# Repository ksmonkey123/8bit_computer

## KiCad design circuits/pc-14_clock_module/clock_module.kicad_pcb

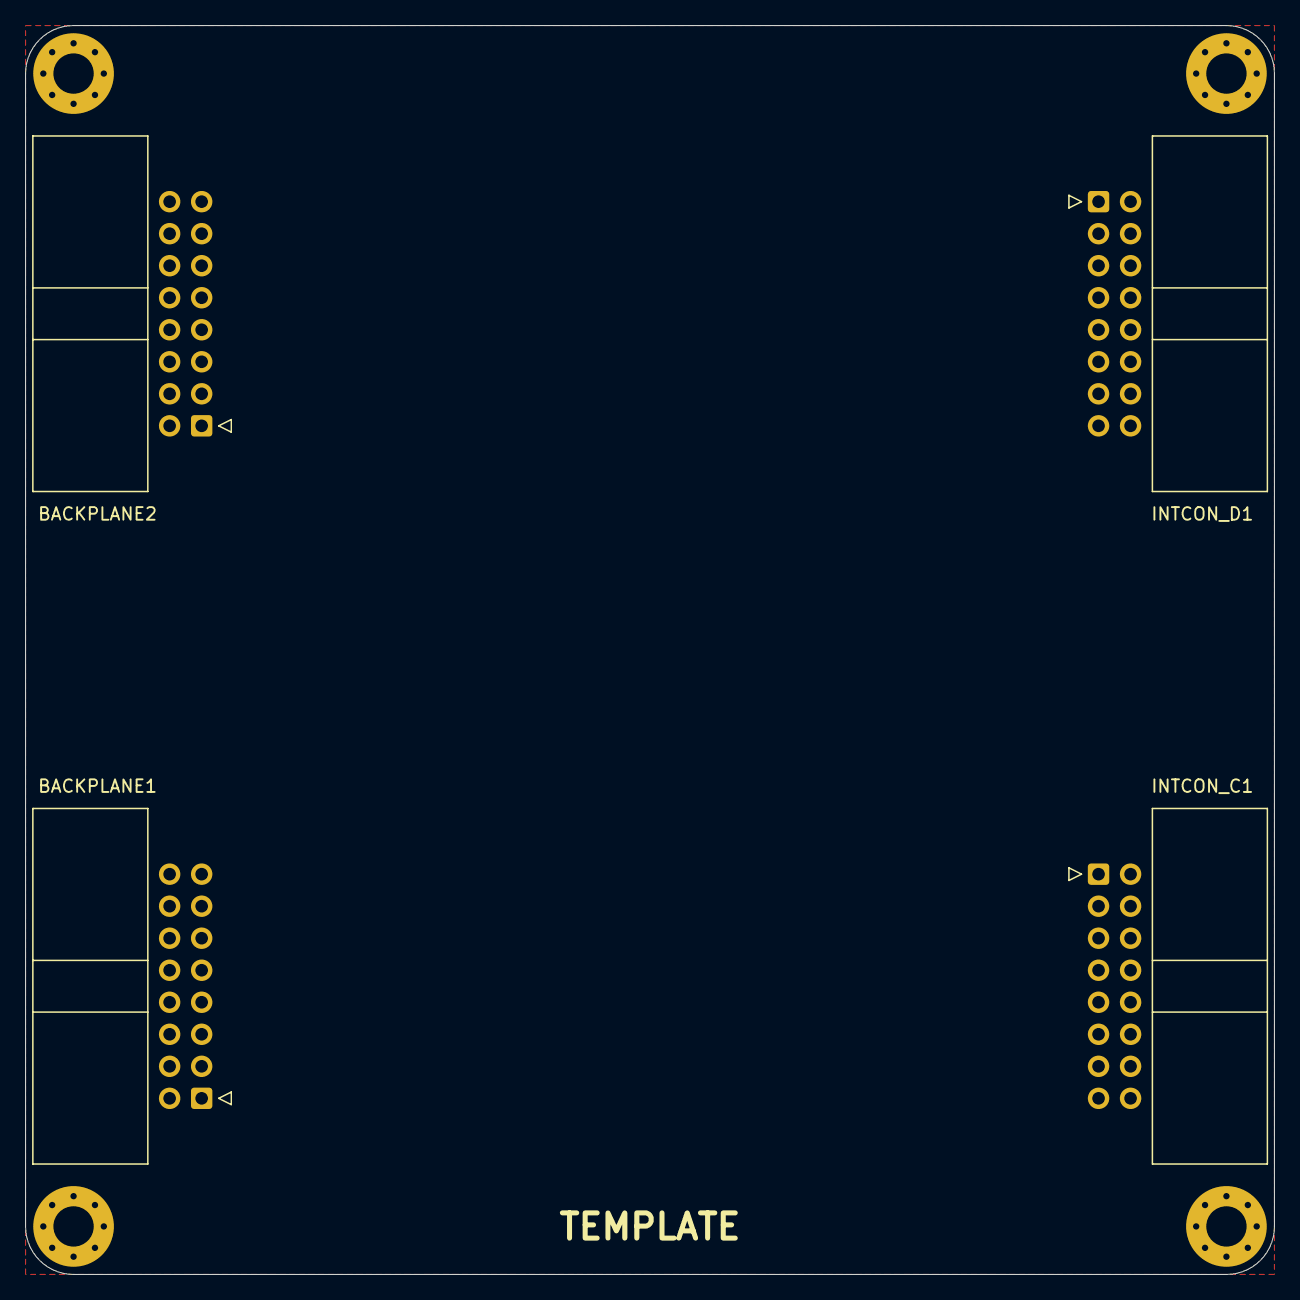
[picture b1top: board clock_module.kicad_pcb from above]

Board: 2 copper layers, 99.1 x 99.1 mm, 8 parts (0 on the bottom side), 4 nets, no tracks yet.

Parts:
BACKPLANE1, BACKPLANE2: Conn_01x16; IDC-Header_2x08_P2.54mm_Horizontal
H1, H2, H3, H4: MountingHole_Pad; MountingHole_3.2mm_M3_Pad_Via
INTCON_C1: Conn_01x16; IDC-Header_2x08_P2.54mm_Horizontal
INTCON_D1: Conn_01x16; IDC-Header_2x08_P2.54mm_Horizontal

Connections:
/clock: BACKPLANE1.1, INTCON_C1.8
/~reset: BACKPLANE1.3, INTCON_D1.12
GND: BACKPLANE1.13, BACKPLANE1.14, BACKPLANE1.15, BACKPLANE1.16, H1.1, H2.1, H3.1, H4.1, INTCON_D1.15, INTCON_D1.16
VCC: BACKPLANE1.9, BACKPLANE1.10, BACKPLANE1.11, BACKPLANE1.12, INTCON_D1.13, INTCON_D1.14

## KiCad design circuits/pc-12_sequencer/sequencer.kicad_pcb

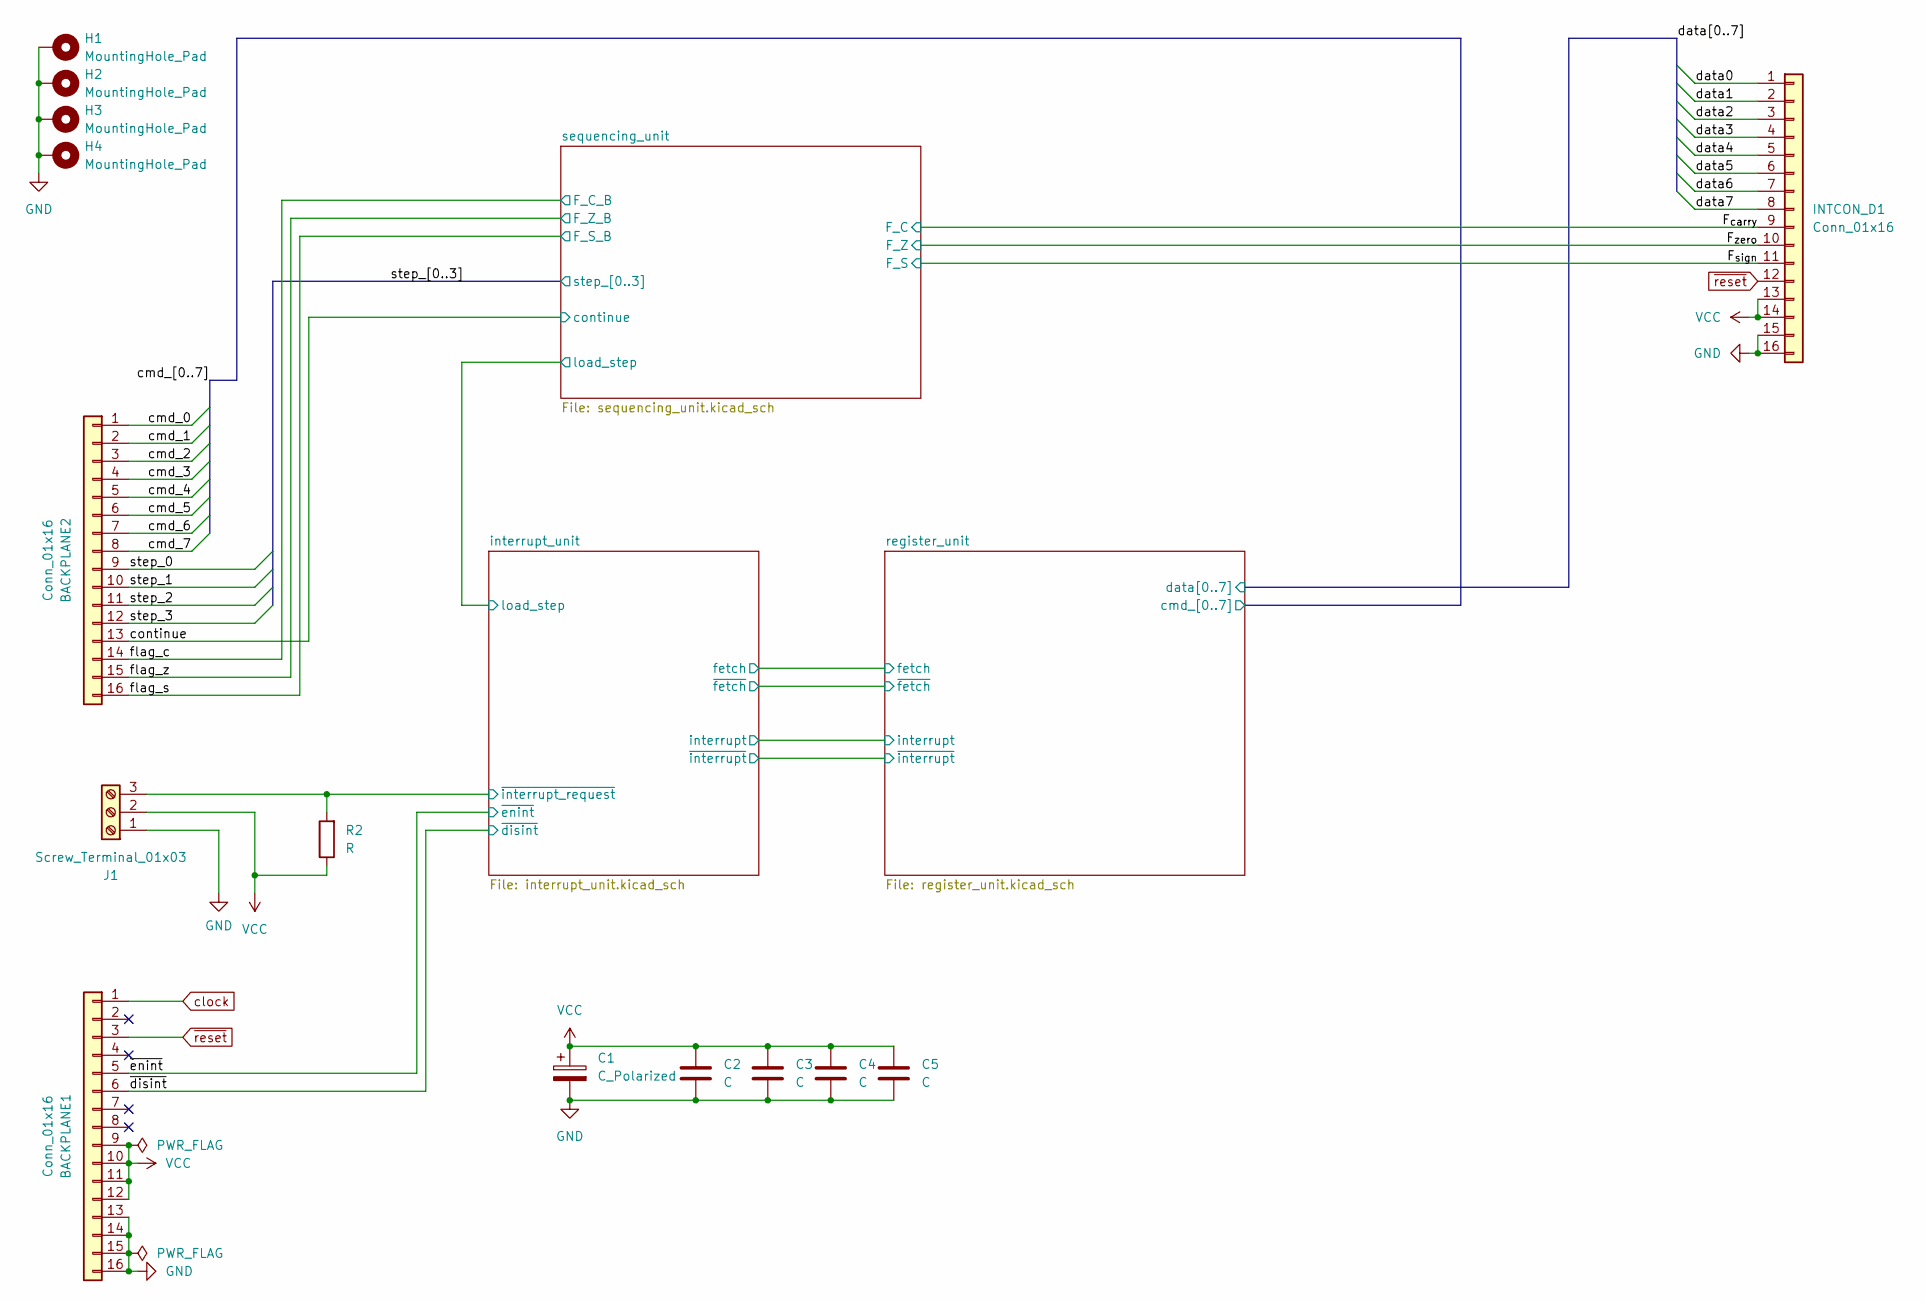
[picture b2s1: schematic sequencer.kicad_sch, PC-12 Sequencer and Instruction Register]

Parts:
BACKPLANE1, BACKPLANE2: Conn_01x16; IDC-Header_2x08_P2.54mm_Horizontal
C1: C_Polarized; CP_Elec_5x5.3
C2, C3, C4, C5: C; C_0603_1608Metric
H1, H2, H3, H4: MountingHole_Pad; MountingHole_3.2mm_M3_Pad_Via
INTCON_D1: Conn_01x16; IDC-Header_2x08_P2.54mm_Horizontal
J1: Screw_Terminal_01x03; TerminalBlock_Xinya_XY308-2.54-3P_1x03_P2.54mm_Horizontal
R2: R; R_0603_1608Metric

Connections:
/F_{carry}: INTCON_D1.9; also elsewhere on the board
/F_{sign}: INTCON_D1.11; also elsewhere on the board
/F_{zero}: INTCON_D1.10; also elsewhere on the board
/cmd_0: BACKPLANE2.1; also elsewhere on the board
/cmd_1: BACKPLANE2.2; also elsewhere on the board
/cmd_2: BACKPLANE2.3; also elsewhere on the board
/cmd_3: BACKPLANE2.4; also elsewhere on the board
/cmd_4: BACKPLANE2.5; also elsewhere on the board
/cmd_5: BACKPLANE2.6; also elsewhere on the board
/cmd_6: BACKPLANE2.7; also elsewhere on the board
/cmd_7: BACKPLANE2.8; also elsewhere on the board
/continue: BACKPLANE2.13; also elsewhere on the board
/data0: INTCON_D1.1; also elsewhere on the board
/data1: INTCON_D1.2; also elsewhere on the board
/data2: INTCON_D1.3; also elsewhere on the board
/data3: INTCON_D1.4; also elsewhere on the board
/data4: INTCON_D1.5; also elsewhere on the board
/data5: INTCON_D1.6; also elsewhere on the board
/data6: INTCON_D1.7; also elsewhere on the board
/data7: INTCON_D1.8; also elsewhere on the board
/flag_c: BACKPLANE2.14; also elsewhere on the board
/flag_s: BACKPLANE2.16; also elsewhere on the board
/flag_z: BACKPLANE2.15; also elsewhere on the board
/interrupt_unit/~interrupt_request: J1.3, R2.2; also elsewhere on the board
/step_0: BACKPLANE2.9; also elsewhere on the board
/step_1: BACKPLANE2.10; also elsewhere on the board
/step_2: BACKPLANE2.11; also elsewhere on the board
/step_3: BACKPLANE2.12; also elsewhere on the board
/~disint: BACKPLANE1.6; also elsewhere on the board
/~enint: BACKPLANE1.5; also elsewhere on the board
GND: BACKPLANE1.13, BACKPLANE1.14, BACKPLANE1.15, BACKPLANE1.16, C1.2, C2.2, C3.2, C4.2, C5.2, H1.1, H2.1, H3.1, H4.1, INTCON_D1.15, INTCON_D1.16, J1.1; also elsewhere on the board
VCC: BACKPLANE1.9, BACKPLANE1.10, BACKPLANE1.11, BACKPLANE1.12, C1.1, C2.1, C3.1, C4.1, C5.1, INTCON_D1.13, INTCON_D1.14, J1.2, R2.1; also elsewhere on the board
clock: BACKPLANE1.1; also elsewhere on the board
~reset: BACKPLANE1.3, INTCON_D1.12; also elsewhere on the board

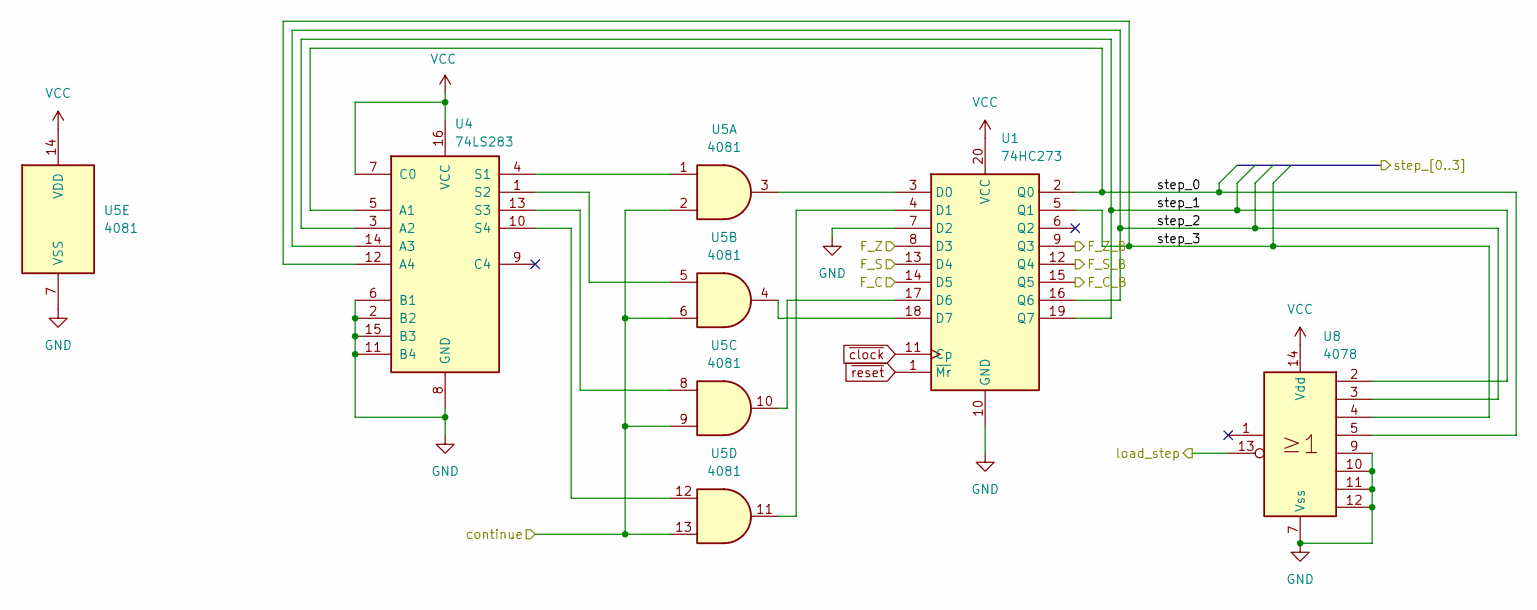
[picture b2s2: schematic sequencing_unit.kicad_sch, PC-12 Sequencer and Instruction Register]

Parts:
U1: 74HC273; DIP-20_W7.62mm
U4: 74LS283; DIP-16_W7.62mm
U5: 4081; DIP-14_W7.62mm
U8: 4078; DIP-14_W7.62mm

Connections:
/F_{carry}: U1.14 (D5); also elsewhere on the board
/F_{sign}: U1.13 (D4); also elsewhere on the board
/F_{zero}: U1.8 (D3); also elsewhere on the board
/continue: U5.2, U5.6, U5.9, U5.13; also elsewhere on the board
/flag_c: U1.15 (Q5); also elsewhere on the board
/flag_s: U1.12 (Q4); also elsewhere on the board
/flag_z: U1.9 (Q3); also elsewhere on the board
/interrupt_unit/load_step: U8.13; also elsewhere on the board
/step_0: U1.2 (Q0), U4.5 (A1), U8.5; also elsewhere on the board
/step_1: U1.19 (Q7), U4.3 (A2), U8.2; also elsewhere on the board
/step_2: U1.16 (Q6), U4.14 (A3), U8.3; also elsewhere on the board
/step_3: U1.5 (Q1), U4.12 (A4), U8.4; also elsewhere on the board
GND: U1.7 (D2), U1.10 (GND), U4.2 (B2), U4.6 (B1), U4.8 (GND), U4.11 (B4), U4.15 (B3), U5.7 (VSS), U8.7 (Vss), U8.9, U8.10, U8.11, U8.12; also elsewhere on the board
unnamed: U1.3 (D0), U5.3
unnamed: U1.4 (D1), U5.11
unnamed: U1.17 (D6), U5.10
unnamed: U1.18 (D7), U5.4
unnamed: U4.4 (S1), U5.1
unnamed: U4.1 (S2), U5.5
unnamed: U4.13 (S3), U5.8
unnamed: U4.10 (S4), U5.12
VCC: U1.20 (VCC), U4.7 (C0), U4.16 (VCC), U5.14 (VDD), U8.14 (Vdd); also elsewhere on the board
~clock: U1.11 (Cp); also elsewhere on the board
~reset: U1.1 (~Mr); also elsewhere on the board

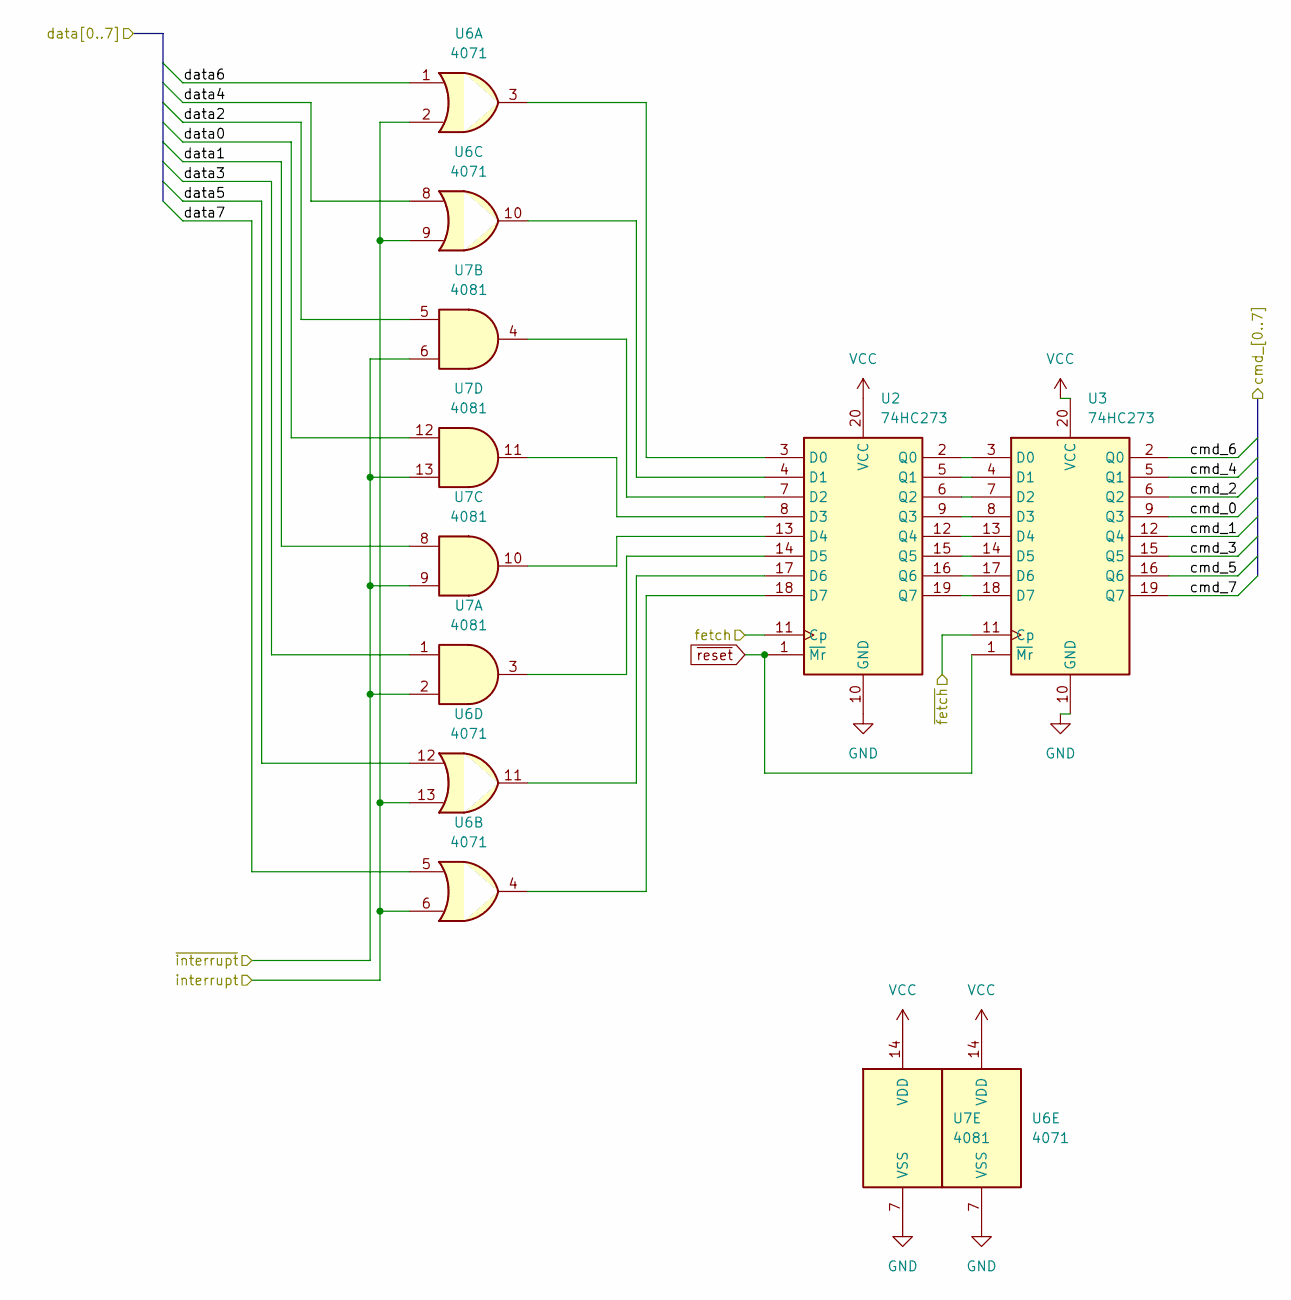
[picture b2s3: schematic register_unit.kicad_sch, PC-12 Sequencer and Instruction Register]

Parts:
U2, U3: 74HC273; DIP-20_W7.62mm
U6: 4071; DIP-14_W7.62mm
U7: 4081; DIP-14_W7.62mm

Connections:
/cmd_0: U3.9 (Q3); also elsewhere on the board
/cmd_1: U3.12 (Q4); also elsewhere on the board
/cmd_2: U3.6 (Q2); also elsewhere on the board
/cmd_3: U3.15 (Q5); also elsewhere on the board
/cmd_4: U3.5 (Q1); also elsewhere on the board
/cmd_5: U3.16 (Q6); also elsewhere on the board
/cmd_6: U3.2 (Q0); also elsewhere on the board
/cmd_7: U3.19 (Q7); also elsewhere on the board
/data0: U7.12; also elsewhere on the board
/data1: U7.8; also elsewhere on the board
/data2: U7.5; also elsewhere on the board
/data3: U7.1; also elsewhere on the board
/data4: U6.8; also elsewhere on the board
/data5: U6.12; also elsewhere on the board
/data6: U6.1; also elsewhere on the board
/data7: U6.5; also elsewhere on the board
/interrupt_unit/fetch: U2.11 (Cp); also elsewhere on the board
/interrupt_unit/interrupt: U6.2, U6.6, U6.9, U6.13; also elsewhere on the board
/interrupt_unit/~fetch: U3.11 (Cp); also elsewhere on the board
/interrupt_unit/~interrupt: U7.2, U7.6, U7.9, U7.13; also elsewhere on the board
GND: U2.10 (GND), U3.10 (GND), U6.7 (VSS), U7.7 (VSS); also elsewhere on the board
unnamed: U2.3 (D0), U6.3
unnamed: U2.4 (D1), U6.10
unnamed: U2.7 (D2), U7.4
unnamed: U2.8 (D3), U7.11
unnamed: U2.13 (D4), U7.10
unnamed: U2.14 (D5), U7.3
unnamed: U2.17 (D6), U6.11
unnamed: U2.18 (D7), U6.4
unnamed: U2.2 (Q0), U3.3 (D0)
unnamed: U2.5 (Q1), U3.4 (D1)
unnamed: U2.6 (Q2), U3.7 (D2)
unnamed: U2.9 (Q3), U3.8 (D3)
unnamed: U2.12 (Q4), U3.13 (D4)
unnamed: U2.15 (Q5), U3.14 (D5)
unnamed: U2.16 (Q6), U3.17 (D6)
unnamed: U2.19 (Q7), U3.18 (D7)
VCC: U2.20 (VCC), U3.20 (VCC), U6.14 (VDD), U7.14 (VDD); also elsewhere on the board
~reset: U2.1 (~Mr), U3.1 (~Mr); also elsewhere on the board

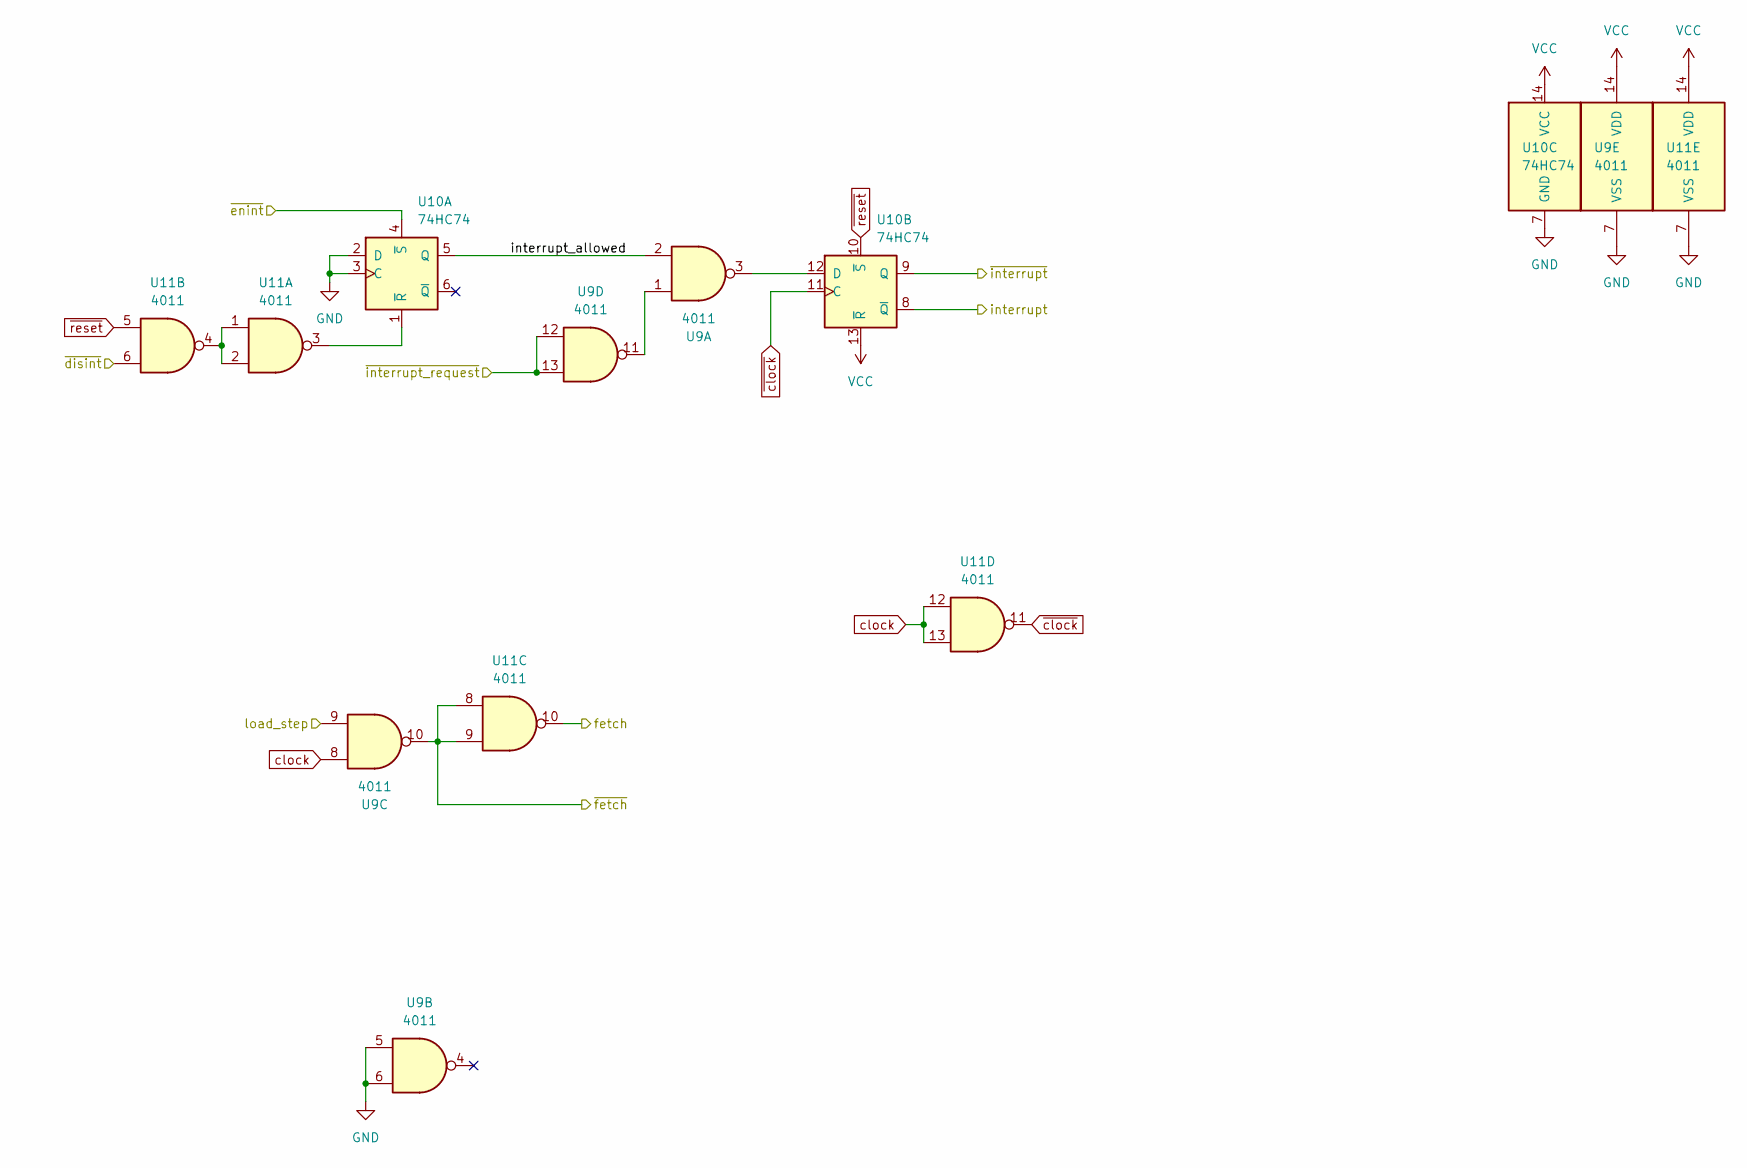
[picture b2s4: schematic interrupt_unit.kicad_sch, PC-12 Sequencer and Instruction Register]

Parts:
U9, U11: 4011; DIP-14_W7.62mm
U10: 74HC74; DIP-14_W7.62mm

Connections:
/interrupt_unit/fetch: U11.10; also elsewhere on the board
/interrupt_unit/interrupt: U10.8 (~Q); also elsewhere on the board
/interrupt_unit/interrupt_allowed: U9.2, U10.5 (Q)
/interrupt_unit/load_step: U9.9; also elsewhere on the board
/interrupt_unit/~fetch: U9.10, U11.8, U11.9; also elsewhere on the board
/interrupt_unit/~interrupt_request: U9.12, U9.13; also elsewhere on the board
/interrupt_unit/~interrupt: U10.9 (Q); also elsewhere on the board
/~disint: U11.6; also elsewhere on the board
/~enint: U10.4 (~S); also elsewhere on the board
GND: U9.5, U9.6, U9.7 (VSS), U10.2 (D), U10.3 (C), U10.7 (GND), U11.7 (VSS); also elsewhere on the board
unnamed: U9.1, U9.11
unnamed: U10.1 (~R), U11.3
unnamed: U9.3, U10.12 (D)
unnamed: U11.1, U11.2, U11.4
VCC: U9.14 (VDD), U10.13 (~R), U10.14 (VCC), U11.14 (VDD); also elsewhere on the board
clock: U9.8, U11.12, U11.13; also elsewhere on the board
~clock: U10.11 (C), U11.11; also elsewhere on the board
~reset: U10.10 (~S), U11.5; also elsewhere on the board

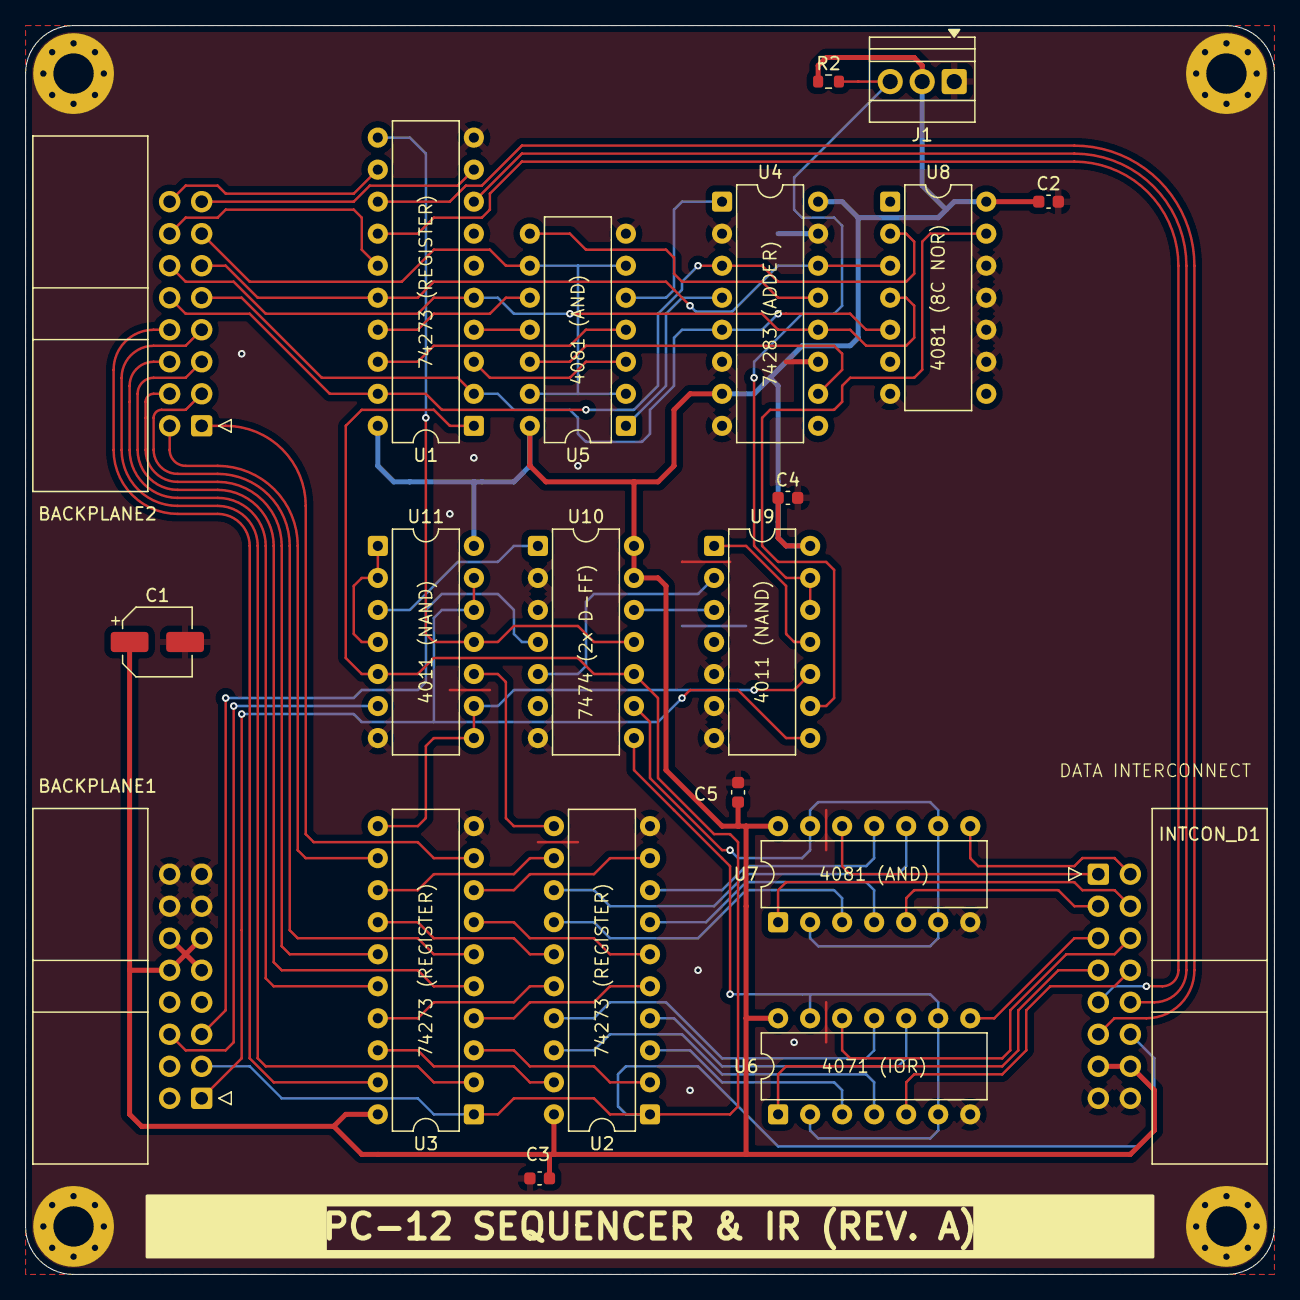
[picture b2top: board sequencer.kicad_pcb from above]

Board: 2 copper layers, 99.1 x 99.1 mm, 25 parts (0 on the bottom side), 69 nets.

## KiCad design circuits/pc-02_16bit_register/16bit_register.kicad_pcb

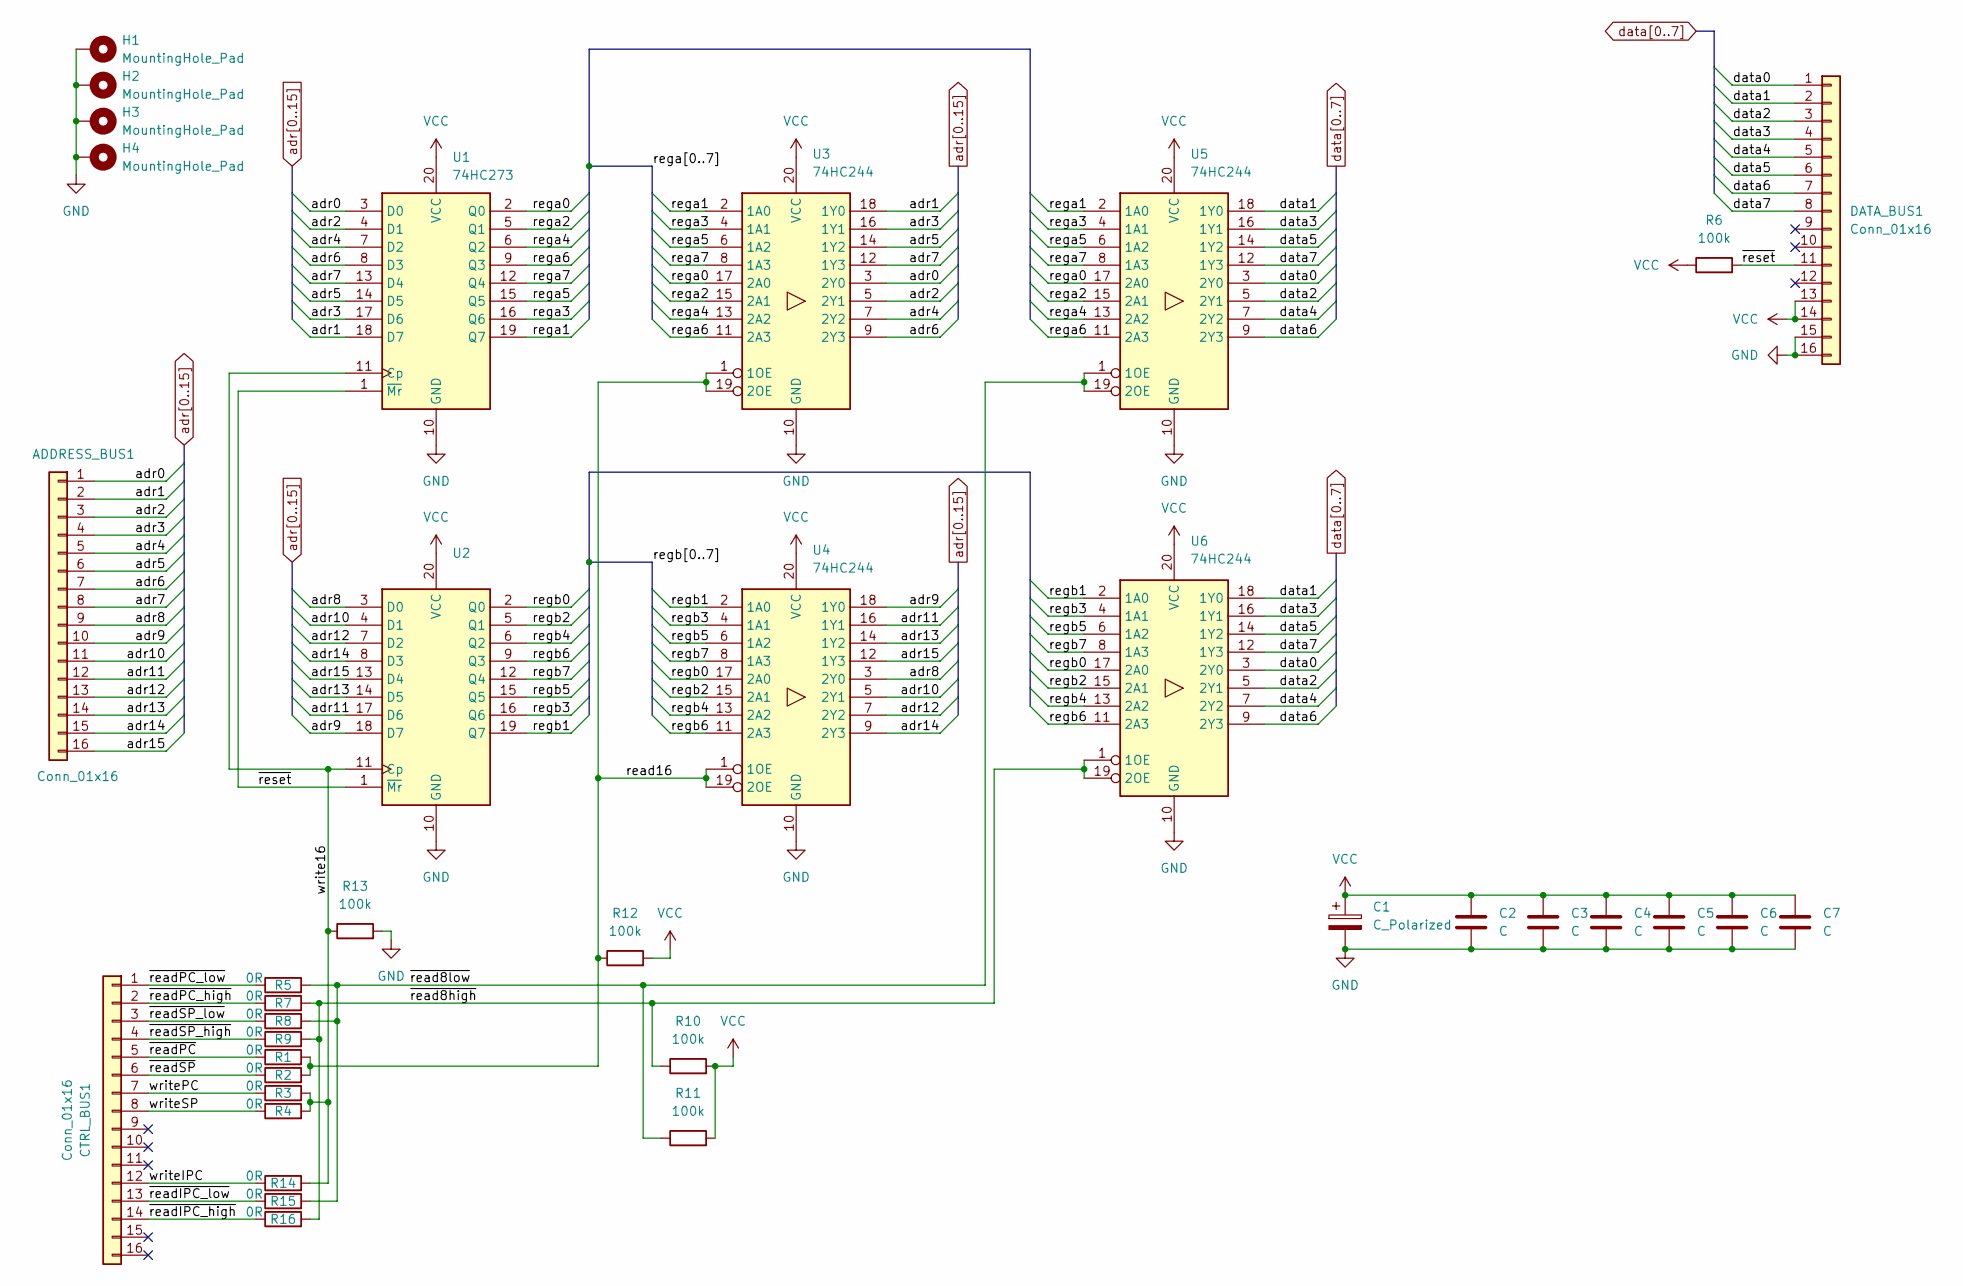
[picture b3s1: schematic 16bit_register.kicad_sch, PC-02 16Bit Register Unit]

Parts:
ADDRESS_BUS1: Conn_01x16; IDC-Header_2x08_P2.54mm_Horizontal
C1: C_Polarized; CP_Elec_5x5.3
C2, C3, C4, C5, C6, C7: C; C_0603_1608Metric
CTRL_BUS1: Conn_01x16; IDC-Header_2x08_P2.54mm_Horizontal
DATA_BUS1: Conn_01x16; IDC-Header_2x08_P2.54mm_Horizontal
H1, H2, H3, H4: MountingHole_Pad; MountingHole_3.2mm_M3_Pad_Via
R1, R2, R3, R4, R5, R7, R8, R9, R14, R15, R16: 0R; R_0603_1608Metric
R6, R10, R11, R12, R13: 100k; R_0603_1608Metric
U1, U2: 74HC273; DIP-20_W7.62mm_LongPads
U3, U4, U5, U6: 74HC244; DIP-20_W7.62mm_LongPads

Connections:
/read16: R1.2, R2.2, R12.1, U3.1 (1OE), U3.19 (2OE), U4.1 (1OE), U4.19 (2OE)
/rega0: U1.2 (Q0), U3.17 (2A0), U5.17 (2A0)
/rega1: U1.19 (Q7), U3.2 (1A0), U5.2 (1A0)
/rega2: U1.5 (Q1), U3.15 (2A1), U5.15 (2A1)
/rega3: U1.16 (Q6), U3.4 (1A1), U5.4 (1A1)
/rega4: U1.6 (Q2), U3.13 (2A2), U5.13 (2A2)
/rega5: U1.15 (Q5), U3.6 (1A2), U5.6 (1A2)
/rega6: U1.9 (Q3), U3.11 (2A3), U5.11 (2A3)
/rega7: U1.12 (Q4), U3.8 (1A3), U5.8 (1A3)
/regb0: U2.2 (Q0), U4.17 (2A0), U6.17 (2A0)
/regb1: U2.19 (Q7), U4.2 (1A0), U6.2 (1A0)
/regb2: U2.5 (Q1), U4.15 (2A1), U6.15 (2A1)
/regb3: U2.16 (Q6), U4.4 (1A1), U6.4 (1A1)
/regb4: U2.6 (Q2), U4.13 (2A2), U6.13 (2A2)
/regb5: U2.15 (Q5), U4.6 (1A2), U6.6 (1A2)
/regb6: U2.9 (Q3), U4.11 (2A3), U6.11 (2A3)
/regb7: U2.12 (Q4), U4.8 (1A3), U6.8 (1A3)
/write16: R3.2, R4.2, R13.1, R14.2, U1.11 (Cp), U2.11 (Cp)
/writeIPC: CTRL_BUS1.12, R14.1
/writePC: CTRL_BUS1.7, R3.1
/writeSP: CTRL_BUS1.8, R4.1
/~read8high: R7.2, R9.2, R10.1, R16.2, U6.1 (1OE), U6.19 (2OE)
/~read8low: R5.2, R8.2, R11.1, R15.2, U5.1 (1OE), U5.19 (2OE)
/~readIPC_high: CTRL_BUS1.14, R16.1
/~readIPC_low: CTRL_BUS1.13, R15.1
/~readPC_high: CTRL_BUS1.2, R7.1
/~readPC_low: CTRL_BUS1.1, R5.1
/~readPC: CTRL_BUS1.5, R1.1
/~readSP_high: CTRL_BUS1.4, R9.1
/~readSP_low: CTRL_BUS1.3, R8.1
/~readSP: CTRL_BUS1.6, R2.1
/~reset: DATA_BUS1.11, R6.2, U1.1 (~Mr), U2.1 (~Mr)
GND: C1.2, C2.2, C3.2, C4.2, C5.2, C6.2, C7.2, DATA_BUS1.15, DATA_BUS1.16, H1.1, H2.1, H3.1, H4.1, R13.2, U1.10 (GND), U2.10 (GND), U3.10 (GND), U4.10 (GND), U5.10 (GND), U6.10 (GND)
VCC: C1.1, C2.1, C3.1, C4.1, C5.1, C6.1, C7.1, DATA_BUS1.13, DATA_BUS1.14, R6.1, R10.2, R11.2, R12.2, U1.20 (VCC), U2.20 (VCC), U3.20 (VCC), U4.20 (VCC), U5.20 (VCC), U6.20 (VCC)
adr0: ADDRESS_BUS1.1, U1.3 (D0), U3.3 (2Y0)
adr1: ADDRESS_BUS1.2, U1.18 (D7), U3.18 (1Y0)
adr2: ADDRESS_BUS1.3, U1.4 (D1), U3.5 (2Y1)
adr3: ADDRESS_BUS1.4, U1.17 (D6), U3.16 (1Y1)
adr4: ADDRESS_BUS1.5, U1.7 (D2), U3.7 (2Y2)
adr5: ADDRESS_BUS1.6, U1.14 (D5), U3.14 (1Y2)
adr6: ADDRESS_BUS1.7, U1.8 (D3), U3.9 (2Y3)
adr7: ADDRESS_BUS1.8, U1.13 (D4), U3.12 (1Y3)
adr8: ADDRESS_BUS1.9, U2.3 (D0), U4.3 (2Y0)
adr9: ADDRESS_BUS1.10, U2.18 (D7), U4.18 (1Y0)
adr10: ADDRESS_BUS1.11, U2.4 (D1), U4.5 (2Y1)
adr11: ADDRESS_BUS1.12, U2.17 (D6), U4.16 (1Y1)
adr12: ADDRESS_BUS1.13, U2.7 (D2), U4.7 (2Y2)
adr13: ADDRESS_BUS1.14, U2.14 (D5), U4.14 (1Y2)
adr14: ADDRESS_BUS1.15, U2.8 (D3), U4.9 (2Y3)
adr15: ADDRESS_BUS1.16, U2.13 (D4), U4.12 (1Y3)
data0: DATA_BUS1.1, U5.3 (2Y0), U6.3 (2Y0)
data1: DATA_BUS1.2, U5.18 (1Y0), U6.18 (1Y0)
data2: DATA_BUS1.3, U5.5 (2Y1), U6.5 (2Y1)
data3: DATA_BUS1.4, U5.16 (1Y1), U6.16 (1Y1)
data4: DATA_BUS1.5, U5.7 (2Y2), U6.7 (2Y2)
data5: DATA_BUS1.6, U5.14 (1Y2), U6.14 (1Y2)
data6: DATA_BUS1.7, U5.9 (2Y3), U6.9 (2Y3)
data7: DATA_BUS1.8, U5.12 (1Y3), U6.12 (1Y3)

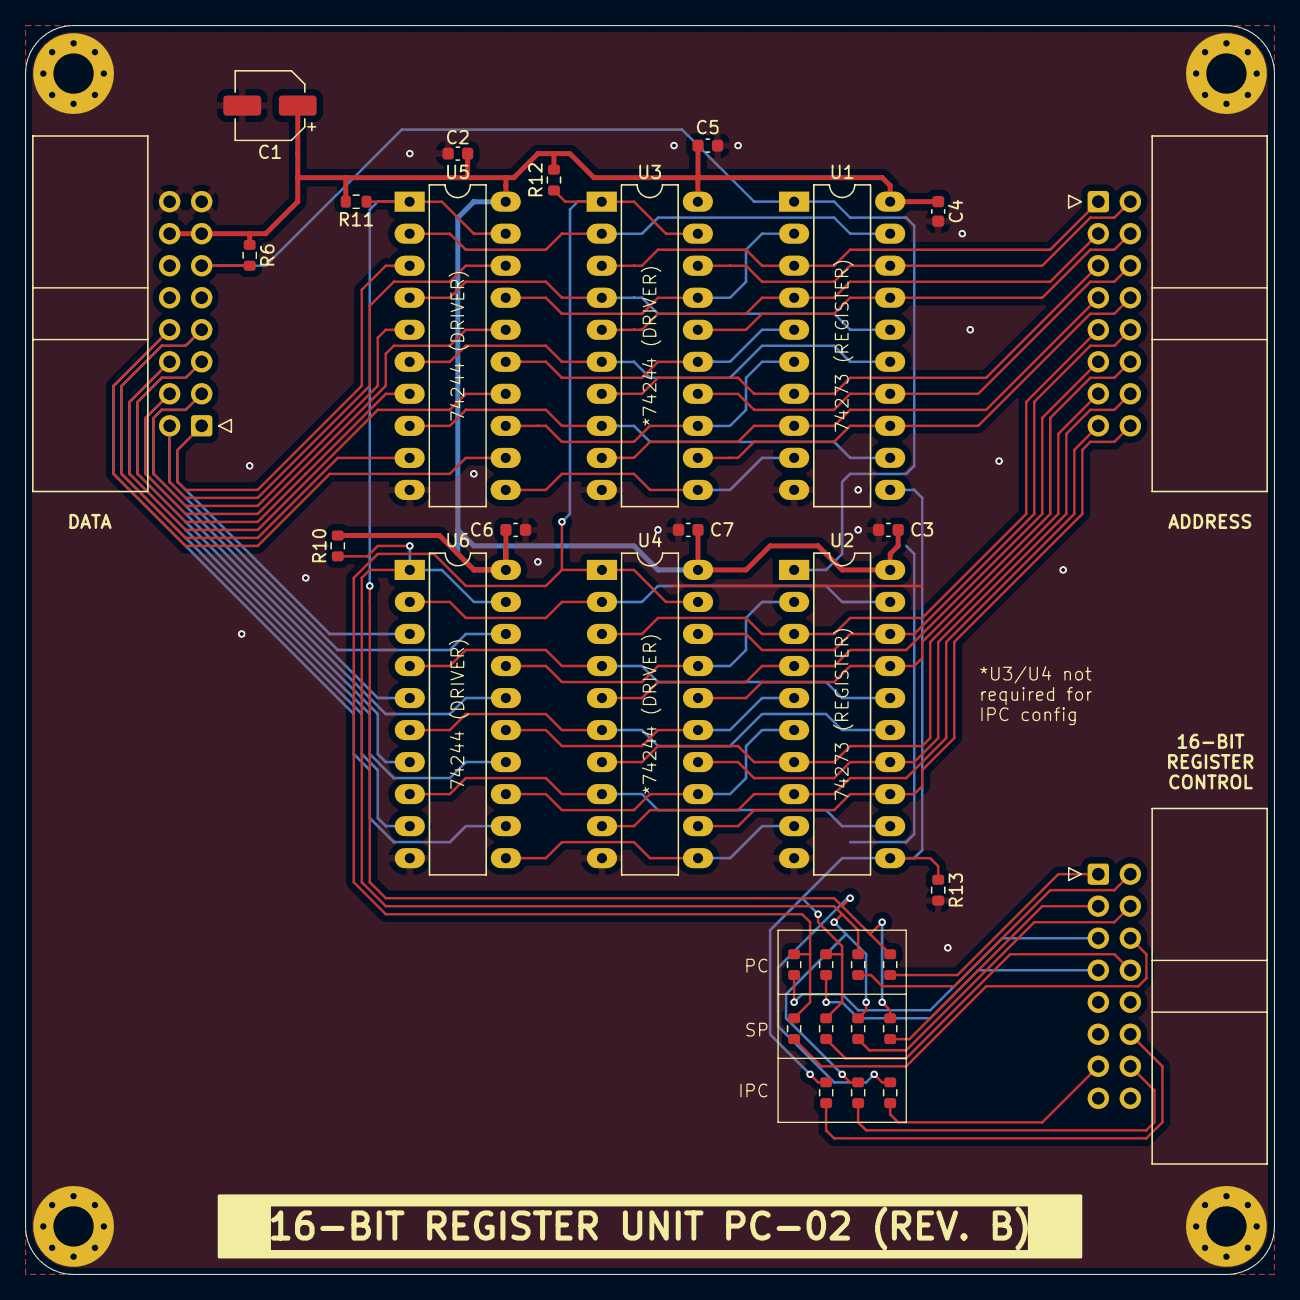
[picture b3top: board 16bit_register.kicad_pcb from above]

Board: 2 copper layers, 99.1 x 99.1 mm, 36 parts (0 on the bottom side), 58 nets.
